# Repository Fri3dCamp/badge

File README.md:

# Fri3d Camp Badge 2018

De Badge voor Fri3d Camp 2018 is in volle ontwikkeling. Op dit ogenblik werken we aan het derde prototype, dat, als alles goed gaat nagenoeg de finale vorm zal hebben.

More to come ...

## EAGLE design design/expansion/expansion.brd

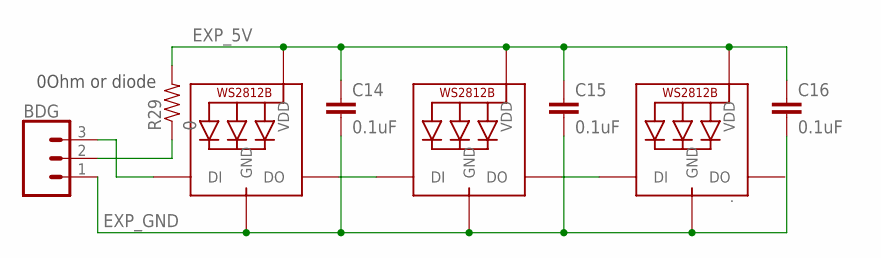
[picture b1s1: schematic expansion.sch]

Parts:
BDG: CONN_03; 1X03
C14, C15, C16: 0.1uF; 0805
R29: 0; 0805
WS1, WS2, WS3: WS2812B5050; WS2812B

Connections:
EXP_5V: C14.1, C15.1, C16.1, R29.2, WS1.1-VDD (VDD), WS2.1-VDD (VDD), WS3.1-VDD (VDD)
EXP_GND: BDG.1, C14.2, C15.2, C16.2, WS1.3-GND (GND), WS2.3-GND (GND), WS3.3-GND (GND)
unnamed: BDG.2, R29.1
unnamed: WS1.2-DOUT (DO), WS2.4-DIN (DI)
unnamed: WS2.2-DOUT (DO), WS3.4-DIN (DI)
unnamed: BDG.3, WS1.4-DIN (DI)

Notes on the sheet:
0Ohm or diode

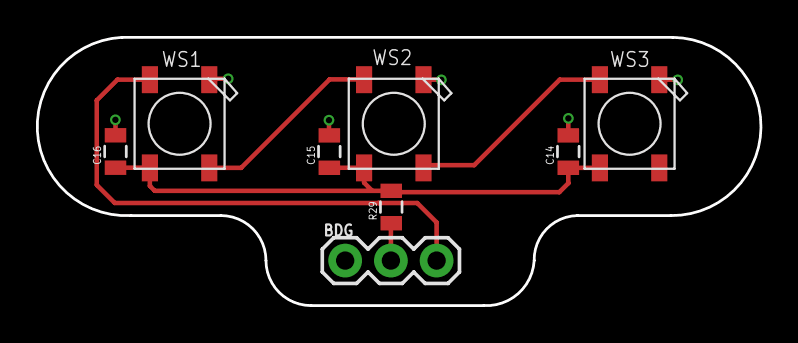
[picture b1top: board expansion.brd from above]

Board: 2 copper layers, 40.2 x 14.9 mm, 8 parts (0 on the bottom side), 6 nets.

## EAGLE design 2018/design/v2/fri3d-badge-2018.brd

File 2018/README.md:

# Fri3d Camp Badge 2018

De Badge voor Fri3d Camp 2018 is in volle ontwikkeling. Op dit ogenblik werken we aan het tweede prototype, dat, als alles goed gaat nagenoeg de finale vorm zal hebben.

More to come ...

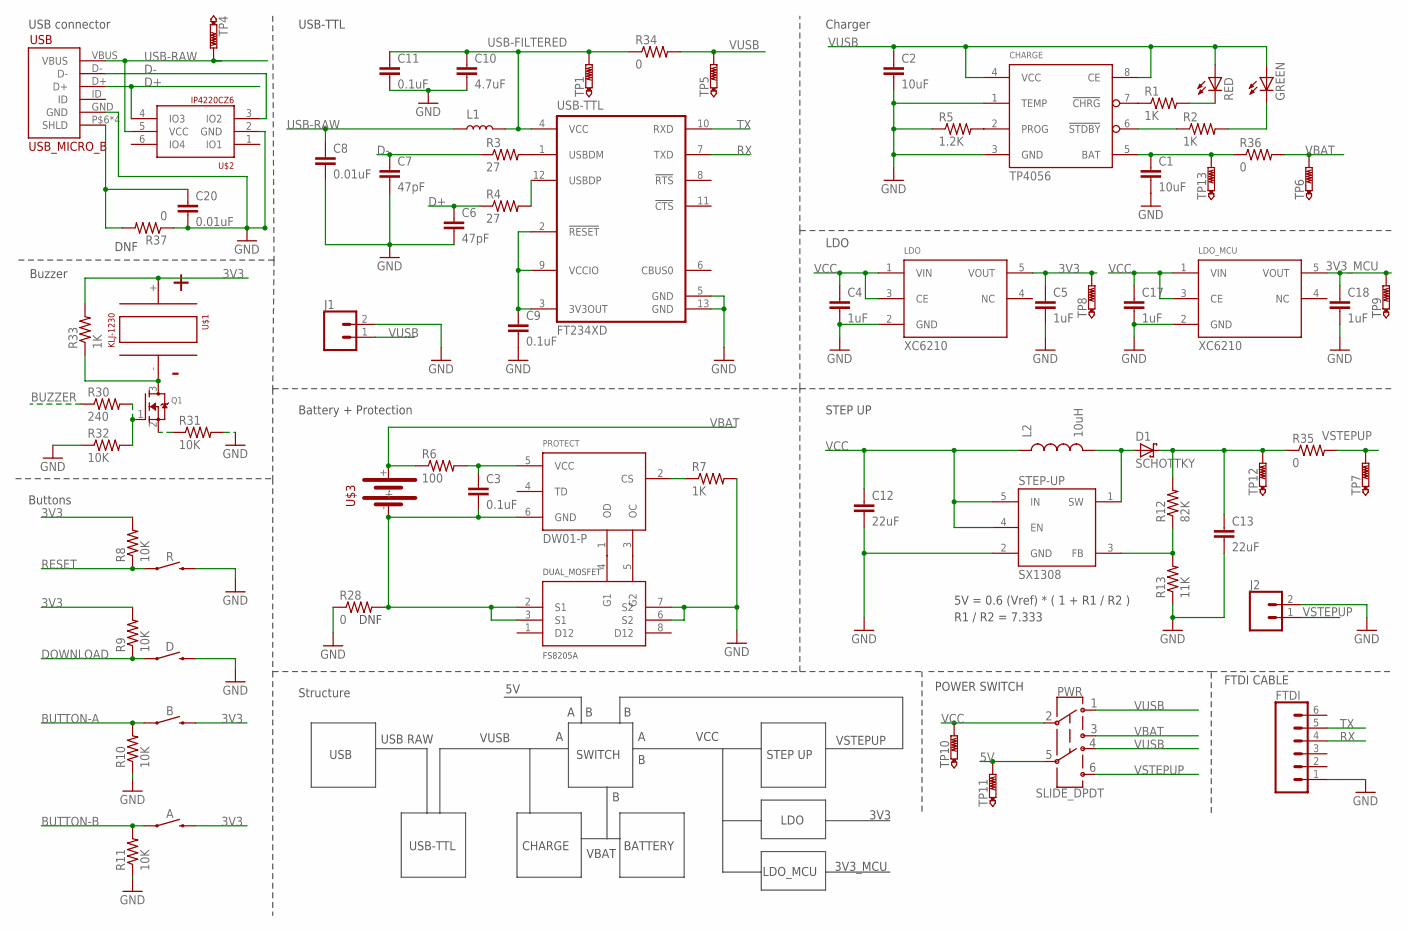
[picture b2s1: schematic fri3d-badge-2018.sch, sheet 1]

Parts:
A: SWITCH-MOMENTARY-4.5MM
B: SWITCH-MOMENTARY-4.5MM
C1, C2: 10uF; 0805
C3, C9, C11: 0.1uF; 0805
C4, C5, C17, C18: 1uF; 0805
C6, C7: 47pF; 0805
C8, C20: 0.01uF; 0805
C10: 4.7uF; 0805
C12, C13: 22uF; 0805
CHARGE: TP4056; SO8
D: SWITCH-MOMENTARY-4.5MM
D1: SCHOTTKY; SOD993
DUAL_MOSFET: FS8205A; TSSOP8
FTDI: CONN_06SILK_FEMALE_PTH; 1X06
GREEN: LEDCHIP-LED0805; CHIP-LED0805
J1, J2: CONN_02; 1X02
L1: INDUCTOR-0805-3.3UH; 0805
L2: 10uH; TYS6045
LDO: XC6210; SOT23-5
LDO_MCU: XC6210; SOT23-5
PROTECT: DW01-P; SOT23-6
PWR: SLIDE_DPDT; SLIDE_SWITCH
Q1: MOSFET-NREFLOW; SOT23
R: SWITCH-MOMENTARY-4.5MM
R1, R2, R7, R33: 1K; 0805
R3, R4: 27; 0805
R5: 1.2K; 0805
R6: 100; 0805
R8, R9, R10, R11, R31, R32: 10K; 0805
R12: 82K; 0805
R13: 11K; 0805
R28, R34, R35, R36, R37: 0; 0805
R30: 240; 0805
RED: LEDCHIP-LED0805; CHIP-LED0805
STEP-UP: SX1308; SOT23-6
TP1, TP4, TP5, TP6, TP7, TP8, TP9, TP10, TP11, TP12, TP13: PTR1B1,27; B1,27
U$1: KLJ-1230
U$2: IP4220CZ6; SOT457R_PHILIPS
U$3: CR18650; BATTERY_HOLDER_18650
USB: USB_MICRO_B
USB-TTL: FT234XD; DFN12

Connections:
3V3: A.3 (2), A.4 (2), B.3 (2), B.4 (2), C5.1, LDO.5 (VOUT), R8.2, R9.2, R33.2, TP8.TP, U$1.+; also elsewhere on the board
3V3_MCU: C18.1, LDO_MCU.5 (VOUT), TP9.TP; also elsewhere on the board
5V: PWR.5, TP11.TP; also elsewhere on the board
BUZZER: R30.1; also elsewhere on the board
D+: C6.1, R4.1, U$2.4 (IO3), USB.D+
D-: C7.1, R3.1, U$2.3 (IO2), USB.D-
DOWNLOAD: D.1, D.2 (1), R9.1; also elsewhere on the board
GND: C1.2, C2.2, C4.2, C5.2, C6.2, C7.2, C8.2, C9.2, C10.2, C11.2, C12.2, C13.2, C17.2, C18.2, C20.2, CHARGE.1 (TEMP), CHARGE.3 (GND), D.3 (2), D.4 (2), DUAL_MOSFET.6 (S2), DUAL_MOSFET.7 (S2), FTDI.1, J1.2, J2.2, LDO.2 (GND), LDO_MCU.2 (GND), R.3 (2), R.4 (2), R5.1, R7.2, R10.1, R11.1, R13.1, R28.1, R31.2, R32.1, R37.1, STEP-UP.2 (GND), U$2.2 (GND), USB.GND, USB-TTL.5 (GND), USB-TTL.13 (GND); also elsewhere on the board
unnamed: C13.1, D1.P$2 (C), R12.2, R35.1, TP12.TP
unnamed: Q1.3 (D), R33.1, U$1.-
unnamed: R3.2, USB-TTL.1 (USBDM)
unnamed: CHARGE.7 (!CHRG!), R1.1
unnamed: R4.2, USB-TTL.12 (USBDP)
unnamed: C9.1, USB-TTL.2 (!RESET!), USB-TTL.3 (3V3OUT), USB-TTL.9 (VCCIO)
unnamed: CHARGE.6 (!STDBY!), R2.1
unnamed: R1.2, RED.C
unnamed: GREEN.C, R2.2
unnamed: CHARGE.2 (PROG), R5.2
unnamed: Q1.1 (G), R30.2, R32.2
unnamed: PROTECT.2 (CS), R7.1
unnamed: C3.1, PROTECT.5 (VCC), R6.2
unnamed: DUAL_MOSFET.4 (G1), PROTECT.1 (OD)
unnamed: DUAL_MOSFET.5 (G2), PROTECT.3 (OC)
unnamed: R12.1, R13.2, STEP-UP.3 (FB)
unnamed: D1.P$1 (A), L2.P$2 (2), STEP-UP.1 (SW)
unnamed: C1.1, CHARGE.5 (BAT), R36.1, TP13.TP
unnamed: C20.1, R37.2, USB.P$6 (SHLD), USB.P$7 (SHLD), USB.P$8 (SHLD), USB.P$9 (SHLD)
unnamed: C3.2, DUAL_MOSFET.2 (S1), DUAL_MOSFET.3 (S1), PROTECT.6 (GND), R28.2, U$3.-
unnamed: Q1.2 (S), R31.1
RESET: R.1, R.2 (1), R8.1; also elsewhere on the board
RX: FTDI.4, USB-TTL.7 (TXD); also elsewhere on the board
TX: FTDI.5, USB-TTL.10 (RXD); also elsewhere on the board
USB-FILTERED: C10.1, C11.1, L1.2, R34.1, TP1.TP, USB-TTL.4 (VCC)
USB-RAW: C8.1, L1.1, TP4.TP, U$2.5 (VCC), USB.VBUS
VBAT: PWR.3, R6.1, R36.2, TP6.TP, U$3.+
VCC: C4.1, C12.1, C17.1, L2.P$1 (1), LDO.1 (VIN), LDO.3 (CE), LDO_MCU.1 (VIN), LDO_MCU.3 (CE), PWR.2, STEP-UP.4 (EN), STEP-UP.5 (IN), TP10.TP
VSTEPUP: J2.1, PWR.4 (6), R35.2, TP7.TP
VUSB: C2.1, CHARGE.4 (VCC), CHARGE.8 (CE), GREEN.A, J1.1, PWR.1, PWR.8 (4), R34.2, RED.A, TP5.TP

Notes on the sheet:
USB connector
Charger
USB-TTL
Battery + Protection
LDO
POWER SWITCH
Buttons
STEP UP
USB
USB RAW
VUSB
CHARGE
VBAT
BATTERY
Structure
VCC
SWITCH
3V3
VSTEPUP
5V = 0.6 (Vref) * ( 1 + R1 / R2 )
R1 / R2 = 7.333
DNF
FTDI CABLE
LDO_MCU
3V3_MCU
Buzzer

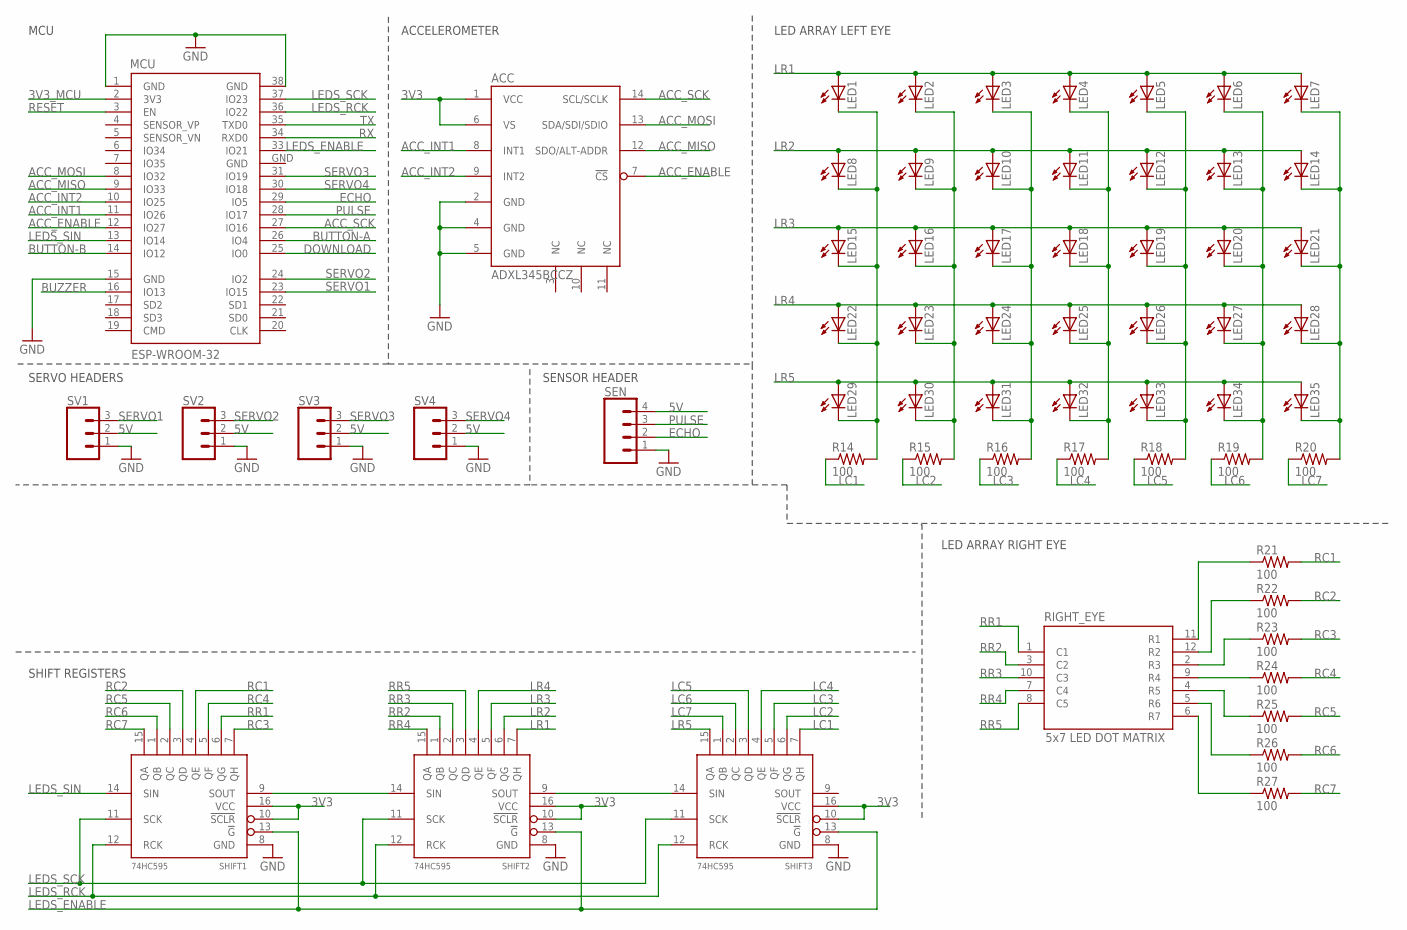
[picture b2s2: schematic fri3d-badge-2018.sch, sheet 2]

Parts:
ACC: ADXL345BCCZ; LGA
LED1, LED2, LED3, LED4, LED5, LED6, LED7, LED8, LED9, LED10, LED11, LED12, LED13, LED14, LED15, LED16, LED17, LED18, LED19, LED20, LED21, LED22, LED23, LED24, LED25, LED26, LED27, LED28, LED29, LED30, LED31, LED32, LED33, LED34, LED35: LEDCHIP-LED0805; CHIP-LED0805
MCU: ESP-WROOM-32
R14, R15, R16, R17, R18, R19, R20, R21, R22, R23, R24, R25, R26, R27: 100; 0805
RIGHT_EYE: 5x7 LED DOT MATRIX; 5X7_DOT_LED_MATRIX
SEN: CONN_04; 1X04
SHIFT1, SHIFT2, SHIFT3: 74HC595; SO16
SV1, SV2, SV3, SV4: CONN_03; 1X03

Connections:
3V3: ACC.1 (VCC), ACC.6 (VS), SHIFT1.10 (!SCLR), SHIFT1.16 (VCC), SHIFT2.10 (!SCLR), SHIFT2.16 (VCC), SHIFT3.10 (!SCLR), SHIFT3.16 (VCC); also elsewhere on the board
3V3_MCU: MCU.2 (3V3); also elsewhere on the board
5V: SEN.4, SV1.2, SV2.2, SV3.2, SV4.2; also elsewhere on the board
ACC_ENABLE: ACC.7 (!CS!), MCU.12 (IO27)
ACC_INT1: ACC.8 (INT1), MCU.11 (IO26)
ACC_INT2: ACC.9 (INT2), MCU.10 (IO25)
ACC_MISO: ACC.12 (SDO/ALT-ADDR), MCU.9 (IO33)
ACC_MOSI: ACC.13 (SDA/SDI/SDIO), MCU.8 (IO32)
ACC_SCK: ACC.14 (SCL/SCLK), MCU.27 (IO16)
BUZZER: MCU.16 (IO13); also elsewhere on the board
DOWNLOAD: MCU.25 (IO0); also elsewhere on the board
ECHO: MCU.29 (IO5), SEN.2
GND: ACC.2 (GND), ACC.4 (GND), ACC.5 (GND), MCU.1 (GND), MCU.15 (GND), MCU.38 (GND), MCU.GND, SEN.1, SHIFT1.8 (GND), SHIFT2.8 (GND), SHIFT3.8 (GND), SV1.1, SV2.1, SV3.1, SV4.1; also elsewhere on the board
LC1: R14.1, SHIFT3.7 (QH)
LC2: R15.1, SHIFT3.6 (QG)
LC3: R16.1, SHIFT3.5 (QF)
LC4: R17.1, SHIFT3.4 (QE)
LC5: R18.1, SHIFT3.3 (QD)
LC6: R19.1, SHIFT3.2 (QC)
LC7: R20.1, SHIFT3.1 (QB)
LEDS_ENABLE: MCU.33 (IO21), SHIFT1.13 (!G), SHIFT2.13 (!G), SHIFT3.13 (!G)
LEDS_RCK: MCU.36 (IO22), SHIFT1.12 (RCK), SHIFT2.12 (RCK), SHIFT3.12 (RCK)
LEDS_SCK: MCU.37 (IO23), SHIFT1.11 (SCK), SHIFT2.11 (SCK), SHIFT3.11 (SCK)
LEDS_SIN: MCU.13 (IO14), SHIFT1.14 (SIN)
LR1: LED1.A, LED2.A, LED3.A, LED4.A, LED5.A, LED6.A, LED7.A, SHIFT2.7 (QH)
LR2: LED8.A, LED9.A, LED10.A, LED11.A, LED12.A, LED13.A, LED14.A, SHIFT2.6 (QG)
LR3: LED15.A, LED16.A, LED17.A, LED18.A, LED19.A, LED20.A, LED21.A, SHIFT2.5 (QF)
LR4: LED22.A, LED23.A, LED24.A, LED25.A, LED26.A, LED27.A, LED28.A, SHIFT2.4 (QE)
LR5: LED29.A, LED30.A, LED31.A, LED32.A, LED33.A, LED34.A, LED35.A, SHIFT3.15 (QA)
unnamed: SHIFT1.9 (SOUT), SHIFT2.14 (SIN)
unnamed: SHIFT2.9 (SOUT), SHIFT3.14 (SIN)
unnamed: R21.1, RIGHT_EYE.11 (R1)
unnamed: R22.1, RIGHT_EYE.12 (R2)
unnamed: LED1.C, LED8.C, LED15.C, LED22.C, LED29.C, R14.2
unnamed: LED2.C, LED9.C, LED16.C, LED23.C, LED30.C, R15.2
unnamed: LED3.C, LED10.C, LED17.C, LED24.C, LED31.C, R16.2
unnamed: LED4.C, LED11.C, LED18.C, LED25.C, LED32.C, R17.2
unnamed: LED5.C, LED12.C, LED19.C, LED26.C, LED33.C, R18.2
unnamed: LED6.C, LED13.C, LED20.C, LED27.C, LED34.C, R19.2
unnamed: LED7.C, LED14.C, LED21.C, LED28.C, LED35.C, R20.2
unnamed: R24.1, RIGHT_EYE.9 (R4)
unnamed: R23.1, RIGHT_EYE.2 (R3)
unnamed: R25.1, RIGHT_EYE.4 (R5)
unnamed: R26.1, RIGHT_EYE.5 (R6)
unnamed: R27.1, RIGHT_EYE.6 (R7)
PULSE: MCU.28 (IO17), SEN.3
RC1: R21.2, SHIFT1.4 (QE)
RC2: R22.2, SHIFT1.3 (QD)
RC3: R23.2, SHIFT1.7 (QH)
RC4: R24.2, SHIFT1.5 (QF)
RC5: R25.2, SHIFT1.2 (QC)
RC6: R26.2, SHIFT1.1 (QB)
RC7: R27.2, SHIFT1.15 (QA)
RESET: MCU.3 (EN); also elsewhere on the board
RR1: RIGHT_EYE.1 (C1), SHIFT1.6 (QG)
RR2: RIGHT_EYE.3 (C2), SHIFT2.1 (QB)
RR3: RIGHT_EYE.10 (C3), SHIFT2.2 (QC)
RR4: RIGHT_EYE.7 (C4), SHIFT2.15 (QA)
RR5: RIGHT_EYE.8 (C5), SHIFT2.3 (QD)
RX: MCU.34 (RXD0); also elsewhere on the board
SERVO1: MCU.23 (IO15), SV1.3
SERVO2: MCU.24 (IO2), SV2.3
SERVO3: MCU.31 (IO19), SV3.3
SERVO4: MCU.30 (IO18), SV4.3
TX: MCU.35 (TXD0); also elsewhere on the board

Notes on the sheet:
LED ARRAY LEFT EYE
LED ARRAY RIGHT EYE
SHIFT REGISTERS
MCU
ACCELEROMETER
SERVO HEADERS
SENSOR HEADER

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
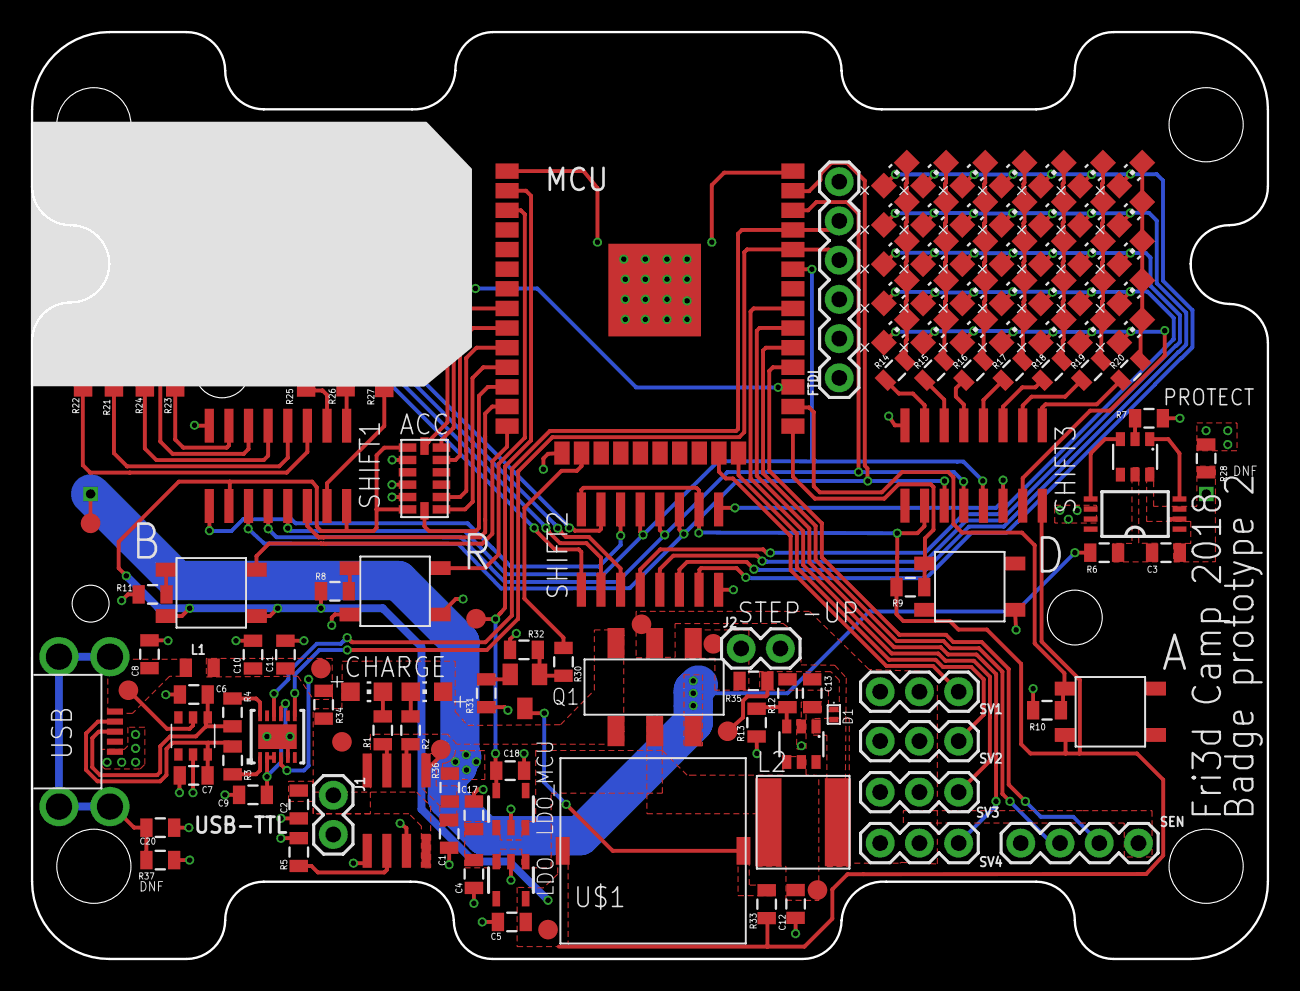
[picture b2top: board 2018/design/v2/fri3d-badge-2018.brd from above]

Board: 2 copper layers, 80.0 x 60.0 mm, 134 parts (1 on the bottom side), 96 nets.

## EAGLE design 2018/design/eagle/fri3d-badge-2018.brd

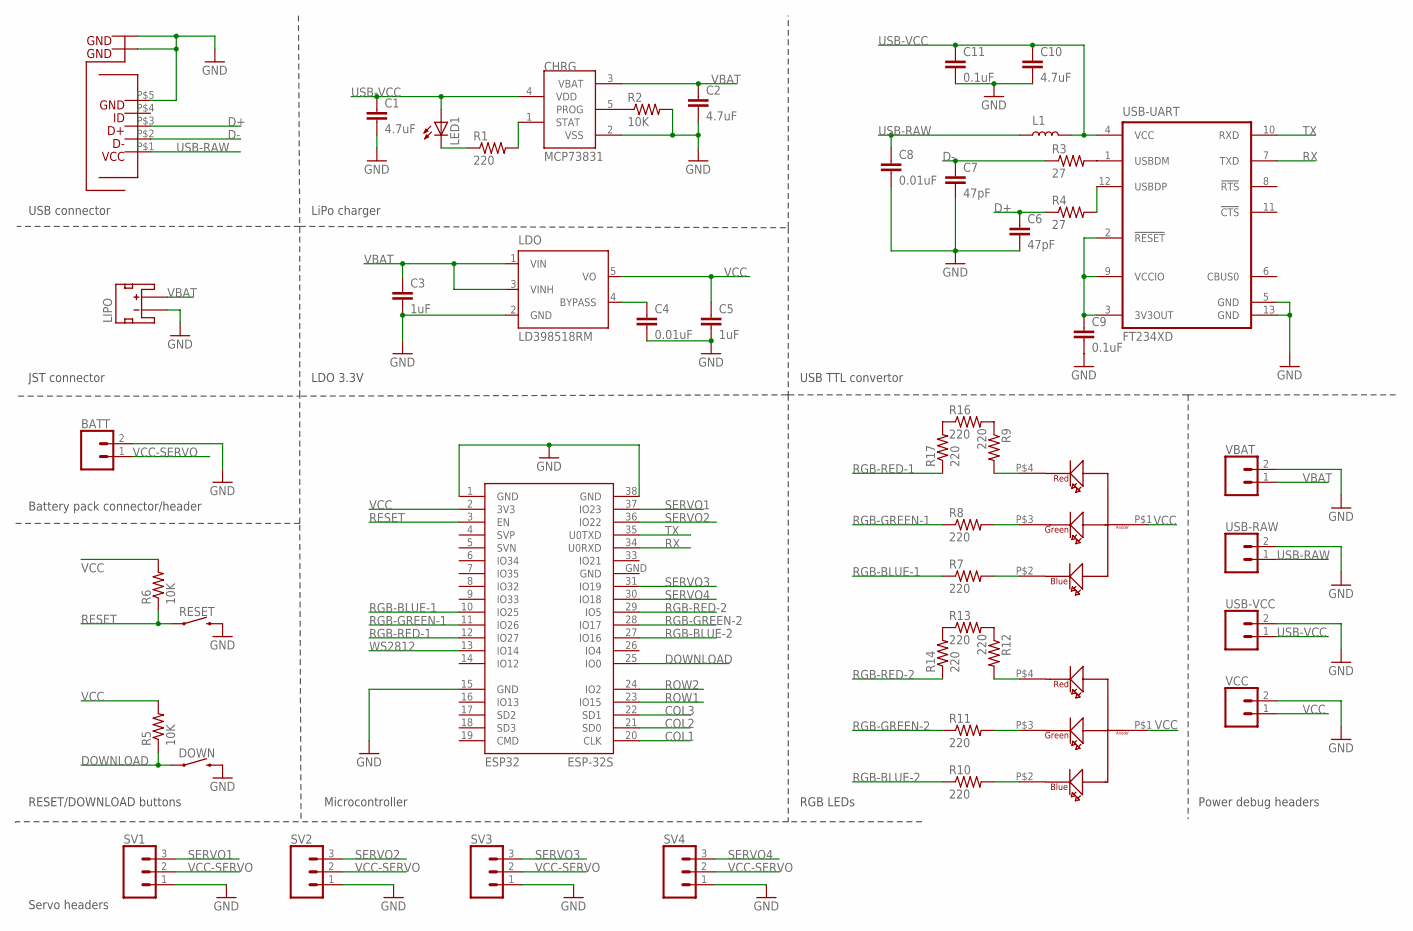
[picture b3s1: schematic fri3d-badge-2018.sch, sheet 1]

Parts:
BATT: CONN_02; 1X02
C1, C2, C10: 4.7uF; 0805
C3, C5: 1uF; 0805
C4, C8: 0.01uF; 0805
C6, C7: 47pF; 0805
C9, C11: 0.1uF; 0805
CHRG: MCP73831; SOT23-5L
DOWN: MOMENTARY-SWITCH-SPST-PTH-6.0MM; TACTILE_SWITCH_PTH_6.0MM
ESP32: ESP-32S
L1: INDUCTOR-0805-3.3UH; 0805
LDO: LD398518RM; SOT23-5L
LED1: LEDCHIP-LED0805; CHIP-LED0805
LIPO: JST_2MM_MALE; JST-2-SMD
R1, R7, R8, R9, R10, R11, R12, R13, R14, R16, R17: 220; 0805
R2, R5, R6: 10K; 0805
R3, R4: 27; 0805
RESET: MOMENTARY-SWITCH-SPST-PTH-6.0MM; TACTILE_SWITCH_PTH_6.0MM
SV1, SV2, SV3, SV4: CONN_03; 1X03
U$1, U$4: DRAGAN-PERSONAL_AVAGO-RGB-LED
U$5: OCTA-CORE_MCIRO-USB2MOUSER; OCTA-CORE_MICRO-USB2
USB-RAW: CONN_02; 1X02
USB-UART: FT234XD; DFN12
USB-VCC: CONN_02; 1X02
VBAT: CONN_02; 1X02
VCC: CONN_02; 1X02

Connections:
COL1: ESP32.20 (CLK); also elsewhere on the board
COL2: ESP32.21 (SD0); also elsewhere on the board
COL3: ESP32.22 (SD1); also elsewhere on the board
D+: C6.1, R4.1, U$5.P$3
D-: C7.1, R3.1, U$5.P$2
DOWNLOAD: DOWN.1, ESP32.25 (IO0), R5.1
GND: BATT.2, C1.2, C2.2, C3.2, C4.2, C5.2, C6.2, C7.2, C8.2, C9.2, C10.2, C11.2, CHRG.2 (VSS), DOWN.3 (2), ESP32.1 (GND), ESP32.15 (GND), ESP32.38 (GND), ESP32.GND, LDO.2 (GND), LIPO.1 (-), R2.2, RESET.3 (2), SV1.1, SV2.1, SV3.1, SV4.1, U$5.P$5, U$5.P$6, U$5.P$7, U$5.P$8, U$5.P$9, U$5.P$10, U$5.P$11, U$5.P$12, U$5.P$13, USB-RAW.2, USB-UART.5 (GND), USB-UART.13 (GND), USB-VCC.2, VBAT.2, VCC.2; also elsewhere on the board
unnamed: CHRG.5 (PROG), R2.1
unnamed: R3.2, USB-UART.1 (USBDM)
unnamed: CHRG.1 (STAT), R1.2
unnamed: LED1.C, R1.1
unnamed: R4.2, USB-UART.12 (USBDP)
unnamed: C9.1, USB-UART.2 (!RESET!), USB-UART.3 (3V3OUT), USB-UART.9 (VCCIO)
unnamed: C4.1, LDO.4 (BYPASS)
unnamed: R12.1, R13.2
unnamed: R13.1, R14.2
unnamed: R11.2, U$1.P$3
unnamed: R9.1, R16.2
unnamed: R16.1, R17.2
unnamed: R12.2, U$1.P$4
unnamed: R10.2, U$1.P$2
unnamed: R9.2, U$4.P$4
unnamed: R8.2, U$4.P$3
unnamed: R7.2, U$4.P$2
RESET: ESP32.3 (EN), R6.1, RESET.1
RGB-BLUE-1: ESP32.10 (IO25), R7.1
RGB-BLUE-2: ESP32.27 (IO16), R10.1
RGB-GREEN-1: ESP32.11 (IO26), R8.1
RGB-GREEN-2: ESP32.28 (IO17), R11.1
RGB-RED-1: ESP32.12 (IO27), R17.1
RGB-RED-2: ESP32.29 (IO5), R14.1
ROW1: ESP32.23 (IO15); also elsewhere on the board
ROW2: ESP32.24 (IO2); also elsewhere on the board
RX: ESP32.34 (U0RXD), USB-UART.7 (TXD)
SERVO1: ESP32.37 (IO23), SV1.3
SERVO2: ESP32.36 (IO22), SV2.3
SERVO3: ESP32.31 (IO19), SV3.3
SERVO4: ESP32.30 (IO18), SV4.3
TX: ESP32.35 (U0TXD), USB-UART.10 (RXD)
USB-RAW: C8.1, L1.1, U$5.P$1, USB-RAW.1
USB-VCC: C1.1, C10.1, C11.1, CHRG.4 (VDD), L1.2, LED1.A, USB-UART.4 (VCC), USB-VCC.1
VBAT: C2.1, C3.1, CHRG.3 (VBAT), LDO.1 (VIN), LDO.3 (VINH), LIPO.2 (+), VBAT.1
VCC: C5.1, ESP32.2 (3V3), LDO.5 (VO), R5.2, R6.2, U$1.P$1, U$4.P$1, VCC.1; also elsewhere on the board
VCC-SERVO: BATT.1, SV1.2, SV2.2, SV3.2, SV4.2
WS2812: ESP32.13 (IO14); also elsewhere on the board

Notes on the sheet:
USB connector
LiPo charger
USB TTL convertor
LDO 3.3V
JST connector
RESET/DOWNLOAD buttons
Microcontroller
RGB LEDs
Servo headers
Power debug headers
Battery pack connector/header

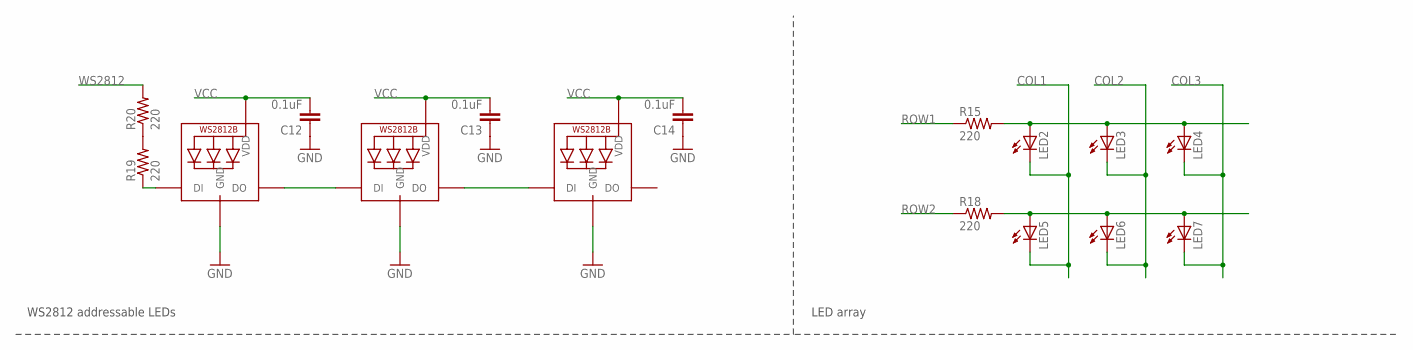
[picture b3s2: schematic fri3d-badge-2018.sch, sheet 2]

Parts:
C12, C13, C14: 0.1uF; 0805
LED2, LED3, LED4, LED5, LED6, LED7: LEDCHIP-LED0805; CHIP-LED0805
R15, R18, R19, R20: 220; 0805
WS1, WS2, WS3: WS2812B5050; WS2812B

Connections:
COL1: LED2.C, LED5.C; also elsewhere on the board
COL2: LED3.C, LED6.C; also elsewhere on the board
COL3: LED4.C, LED7.C; also elsewhere on the board
GND: C12.1, C13.1, C14.1, WS1.3-GND (GND), WS2.3-GND (GND), WS3.3-GND (GND); also elsewhere on the board
unnamed: WS1.2-DOUT (DO), WS2.4-DIN (DI)
unnamed: WS2.2-DOUT (DO), WS3.4-DIN (DI)
unnamed: LED2.A, LED3.A, LED4.A, R15.2
unnamed: LED5.A, LED6.A, LED7.A, R18.2
unnamed: R19.1, WS1.4-DIN (DI)
unnamed: R19.2, R20.1
ROW1: R15.1; also elsewhere on the board
ROW2: R18.1; also elsewhere on the board
VCC: C12.2, C13.2, C14.2, WS1.1-VDD (VDD), WS2.1-VDD (VDD), WS3.1-VDD (VDD); also elsewhere on the board
WS2812: R20.2; also elsewhere on the board

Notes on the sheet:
WS2812 addressable LEDs
LED array

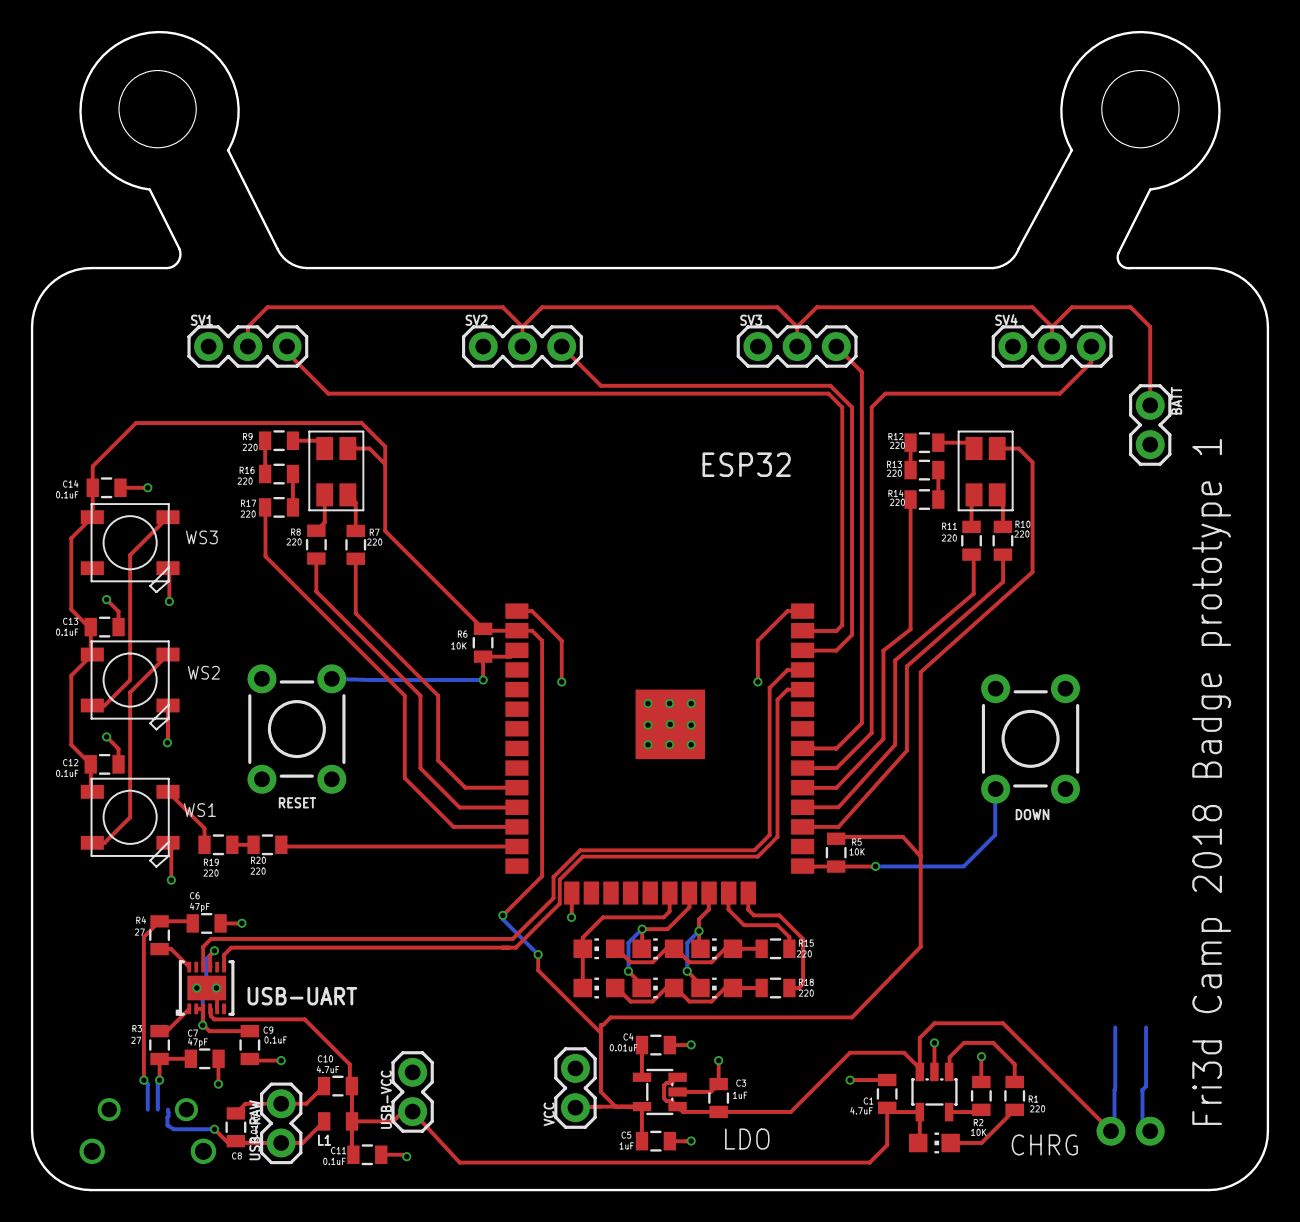
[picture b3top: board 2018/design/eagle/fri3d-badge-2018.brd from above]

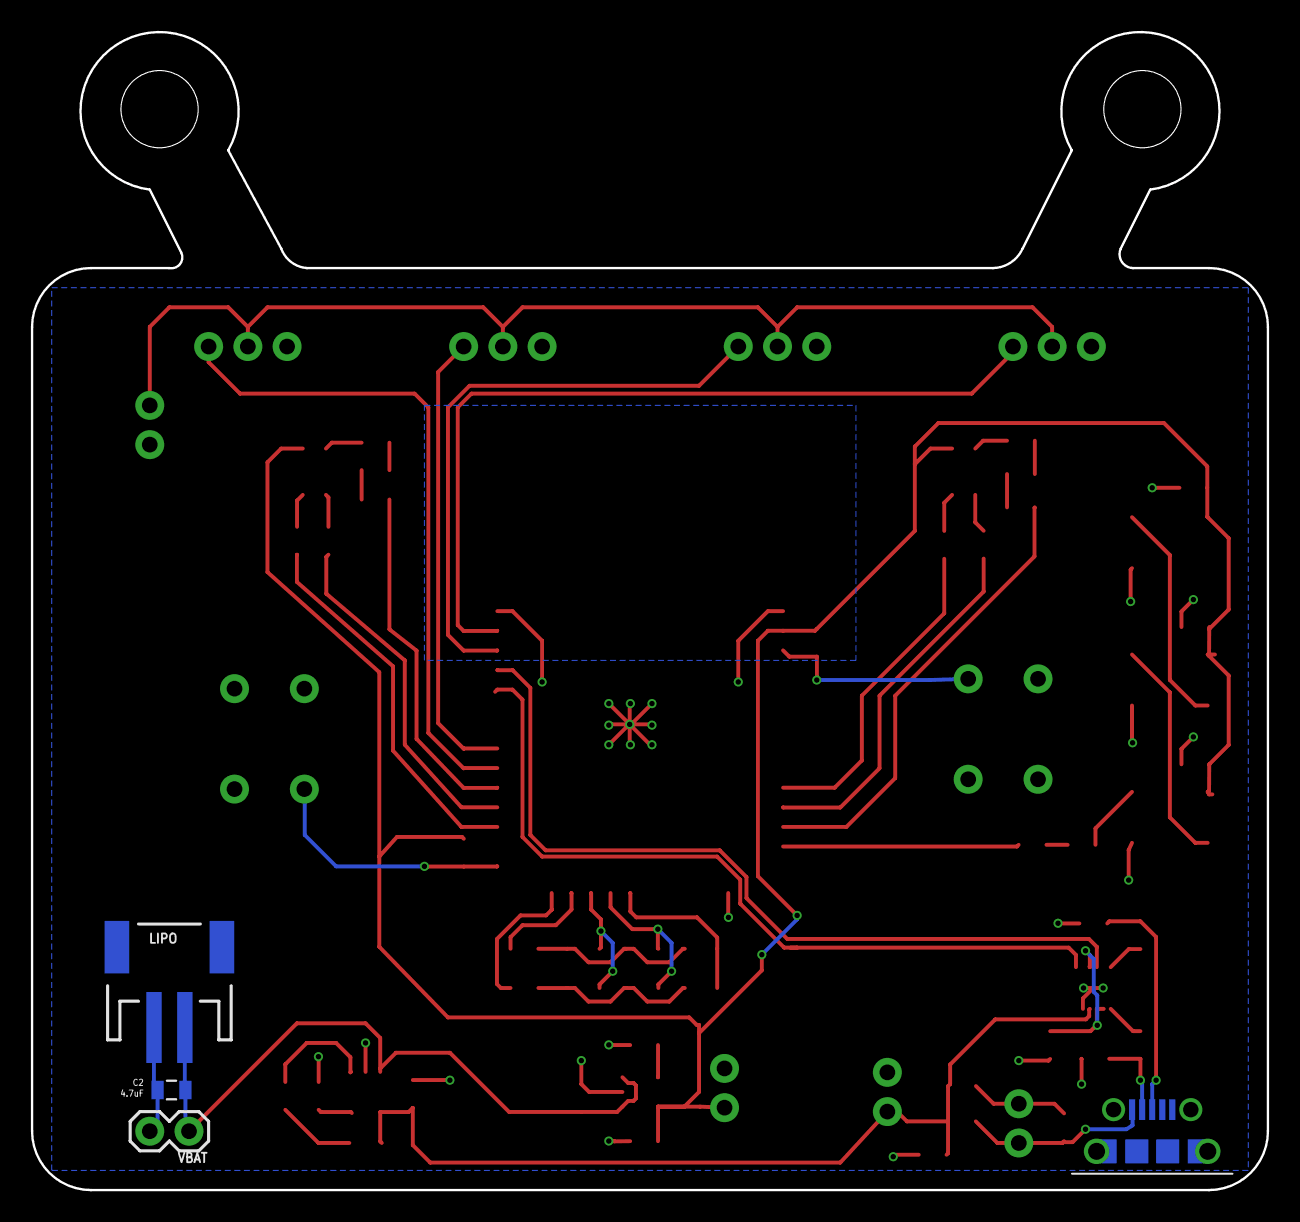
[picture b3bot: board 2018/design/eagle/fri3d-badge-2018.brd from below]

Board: 2 copper layers, 80.0 x 75.0 mm, 64 parts (4 on the bottom side), 51 nets.

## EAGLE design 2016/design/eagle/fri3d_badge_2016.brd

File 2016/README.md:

# Fri3d Camp Badge 2016

Bij het ontwerp van de badge voor Fri3d Camp 2016 zijn we vertrokken van drie principes:

1. Een hoge _hack_-baarheid.
2. Leerzaam voor beginners.
3. Interactief.

Daarom brengt de badge het Arduino platform samen met infra-rode stralen om een eenvoudig Fri3d Camp draadloos (IR) netwerk te maken.

Het Arduino platform laat iedereen toe om de software van de badge aan te passen, of er iets totaal anders mee te doen. Naast de badge-functie voor Fri3d Camp, brengen we alle andere mogelijke functionaliteit van de microcontroller naar buiten, zodat de badge, na het kamp, letterlijk kan dienen als jouw eigen Arduino ontwikkel-bord.

Aan de hand van de IR componenten en bijhorende software kunnen de elementaire aspecten van draadloze communicatie uitgelegd worden.

### Meta-Leerzaam

Dit ontwerp was mijn eerste SMD-gebaseerde project en het is op zich al een leerzame ervaring. Daarom bevat deze repository tevens een [design dagboek](design/dagboek.md) waarin ik alle stappen van het proces beschrijf.

## Hardware Design

Twee bestaande projecten kunnen beschouwd worden als de spreekwoordelijke ouders van de badge: 

* [Arduino Pro Micro - 3.3V/8MHz van Sparkfun](https://www.sparkfun.com/products/12587)
* [TV B Gone van Mitch Altman](https://cornfieldelectronics.com/tvbgone/tvbg.home.php)

Voeg nog een IR receiver en een RGB LED toe en je hebt alle basis componenten voor een leerzame, interactieve en zeer _hack_-bare Fri3d Camp badge!

## Software

Om zelf aan de slag te gaan met de [software](src/README.md) zo eenvoudig mogelijk te maken, was één van dé belangrijkste aspecten een makkelijke integratie met het Arduino software platform. De mogelijkheid om de badge te programmeren via de Arduino IDE door middel van louter een micro-USB kabel was daarom een noodzaak.

Om het Arduino platform nog verder zo veel mogelijk te gebruiken, hebben we ook gekozen om zo dicht mogelijk bij een bestaand Arduino bord te blijven en zo is de badge in essentie een [Arduino Mirco](https://www.arduino.cc/en/Main/ArduinoBoardMicro) geworden.

Je kan dus onmiddellijk aan de slag, zoals met elke andere Arduino. Daarnaast bevat deze [repository](src/README.md) enkele applicaties specifiek geschreven voor de Fri3d Camp badge, en dit naast een bibliotheek die het aanspreken van de extras makkelijk maakt. Zo vindt je hier:

* dé Fri3d Camp 2016 app
* een implementatie van de TV B Gone applicatie van Mitch Altman
* ...

Als je zelf een nieuwe app maakt die op de Fri3d Camp badge werkt en op een andere, leuke manier gebruik maakt van de IR communicatie en de RGB LED of van andere componenten die je er zelf aan toegevoegd hebt, bezorg ons dan deze code en we voegen ze toe aan deze repository (pull request).

## Credits

De badge werd ontworpen door Christophe VG, samen met de hele Fri3d Camp organisatie, en uitgewerkt met de hulp van Dragan Subotic, Yannick Verbelen, Maarten Weyn, Willy De a Court, Anthony Liekens, Dries Deroeck, Jef Van Den Broeck, Toon Van de Putte,...

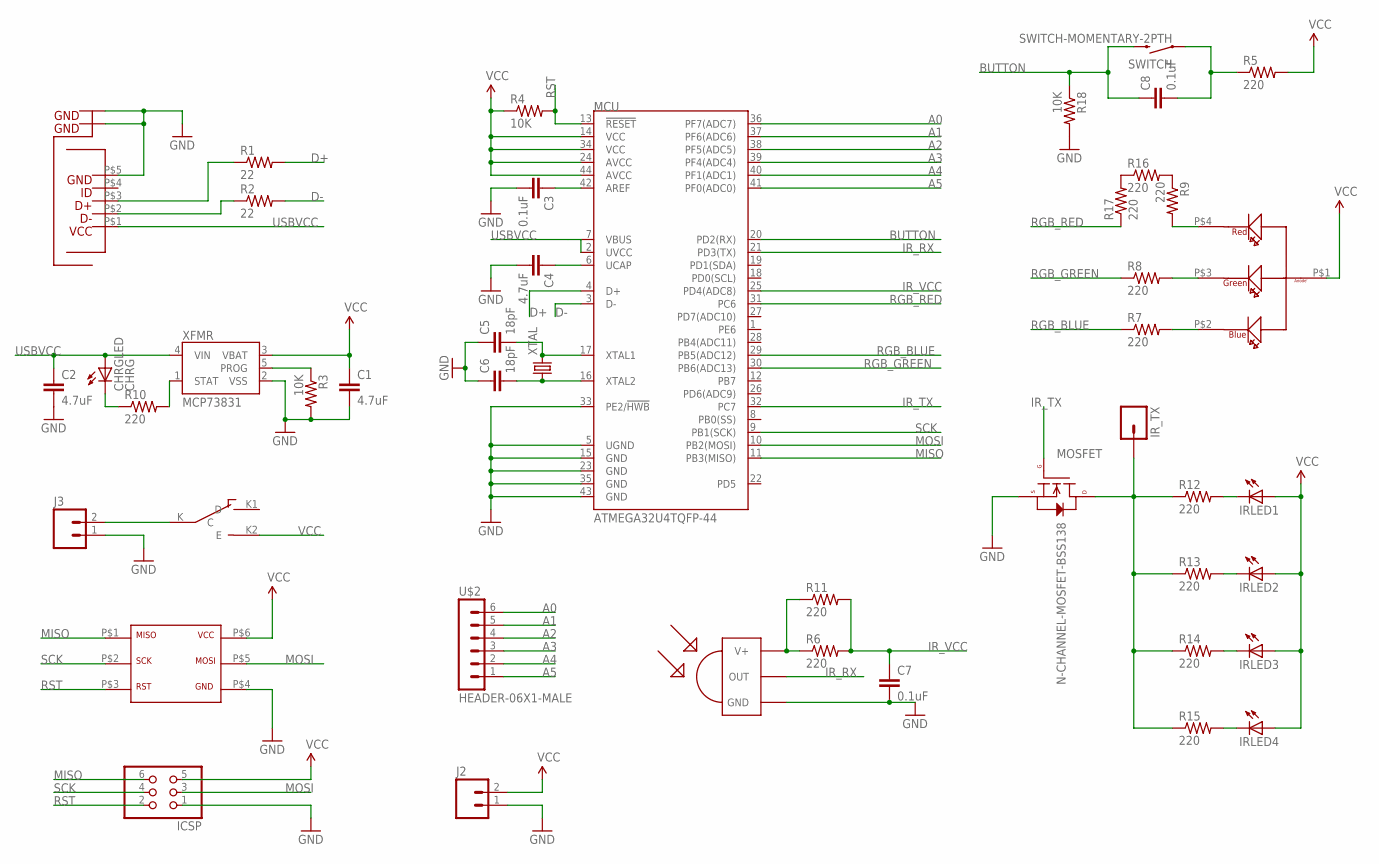
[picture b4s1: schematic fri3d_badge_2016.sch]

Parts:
C1, C2, C4: 4.7uF; 0805
C3, C7, C8: 0.1uF; 0805
C5, C6: 18pF; 0805
CHRGLED: CHRG; CHIPLED_0805
ICSP: PINHD-2X3; 2X03
IRLED1, IRLED2, IRLED3, IRLED4: LEDCHIPLED_0805; CHIPLED_0805
IR_TX: M01PTH; 1X01
J2: M02PTH; 1X02
J3: M02JST-PTH-2; JST-2-PTH
MCU: ATMEGA32U4TQFP-44; TQFP44
MOSFET: N-CHANNEL-MOSFET-BSS138; SOT23-3
R1, R2: 22; 0805
R3, R4, R18: 10K; 0805
R5, R6, R7, R8, R9, R10, R11, R12, R13, R14, R15, R16, R17: 220; 0805
SWITCH: SWITCH-MOMENTARY-2PTH; TACTILE-PTH
U$2: HEADER-06X1-MALE; 06X1-PTH
U$3: TSOP4838; TSOP18XX
U$4: DRAGAN-PERSONAL_AVAGO-RGB-LED
U$5: OCTA-CORE_MCIRO-USB2MOUSER; OCTA-CORE_MICRO-USB2
U$6: SLIDE-SWITCH
U$7: OCTA-CORE_TC2030-IDC
XFMR: MCP73831; SOT23-5
XTAL: CRYSTALHC49S; HC49/S

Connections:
A0: MCU.36 (PF7(ADC7)), U$2.6
A1: MCU.37 (PF6(ADC6)), U$2.5
A2: MCU.38 (PF5(ADC5)), U$2.4
A3: MCU.39 (PF4(ADC4)), U$2.3
A4: MCU.40 (PF1(ADC1)), U$2.2
A5: MCU.41 (PF0(ADC0)), U$2.1
BUTTON: C8.1, MCU.20 (PD2(RX)), R18.1, SWITCH.3 (2)
D+: MCU.4 (D+), R1.2
D-: MCU.3 (D-), R2.2
GND: C1.2, C2.2, C3.2, C4.2, C5.1, C6.1, C7.2, ICSP.1, J2.1, J3.1, MCU.5 (UGND), MCU.15 (GND), MCU.23 (GND), MCU.33 (PE2/!HWB), MCU.35 (GND), MCU.43 (GND), MOSFET.2 (S), R3.2, R18.2, U$3.GND, U$5.P$5, U$5.P$6, U$5.P$7, U$5.P$8, U$5.P$9, U$5.P$10, U$5.P$11, U$5.P$12, U$5.P$13, U$7.P$4, XFMR.2 (VSS)
IR_RX: MCU.21 (PD3(TX)), U$3.OUT
IR_TX: MCU.32 (PC7), MOSFET.1 (G)
IR_VCC: C7.1, MCU.25 (PD4(ADC8)), R6.2, R11.2
MISO: ICSP.6, MCU.11 (PB3(MISO)), U$7.P$1
MOSI: ICSP.3, MCU.10 (PB2(MOSI)), U$7.P$5
unnamed: R2.1, U$5.P$2
unnamed: R1.1, U$5.P$3
unnamed: C8.2, R5.1, SWITCH.1
unnamed: C4.1, MCU.6 (UCAP)
unnamed: R3.1, XFMR.5 (PROG)
unnamed: CHRGLED.C, R10.1
unnamed: C3.1, MCU.42 (AREF)
unnamed: C5.2, MCU.17 (XTAL1), XTAL.2
unnamed: C6.2, MCU.16 (XTAL2), XTAL.1
unnamed: R6.1, R11.1, U$3.VCC (V+)
unnamed: R9.1, R16.2
unnamed: R16.1, R17.2
unnamed: IRLED1.C, R12.2
unnamed: IRLED2.C, R13.2
unnamed: IRLED3.C, R14.2
unnamed: IRLED4.C, R15.2
unnamed: J3.2, U$6.K (C)
unnamed: R9.2, U$4.P$4
unnamed: R8.2, U$4.P$3
unnamed: R7.2, U$4.P$2
unnamed: R10.2, XFMR.1 (STAT)
unnamed: IR_TX.1, MOSFET.3 (D), R12.1, R13.1, R14.1, R15.1
RGB_BLUE: MCU.29 (PB5(ADC12)), R7.1
RGB_GREEN: MCU.30 (PB6(ADC13)), R8.1
RGB_RED: MCU.31 (PC6), R17.1
RST: ICSP.2, MCU.13 (!RESET), R4.2, U$7.P$3
SCK: ICSP.4, MCU.9 (PB1(SCK)), U$7.P$2
USBVCC: C2.1, CHRGLED.A, MCU.2 (UVCC), MCU.7 (VBUS), U$5.P$1, XFMR.4 (VIN)
VCC: C1.1, ICSP.5, IRLED1.A, IRLED2.A, IRLED3.A, IRLED4.A, J2.2, MCU.14 (VCC), MCU.24 (AVCC), MCU.34 (VCC), MCU.44 (AVCC), R4.1, R5.2, U$4.P$1, U$6.K2 (E), U$7.P$6, XFMR.3 (VBAT)

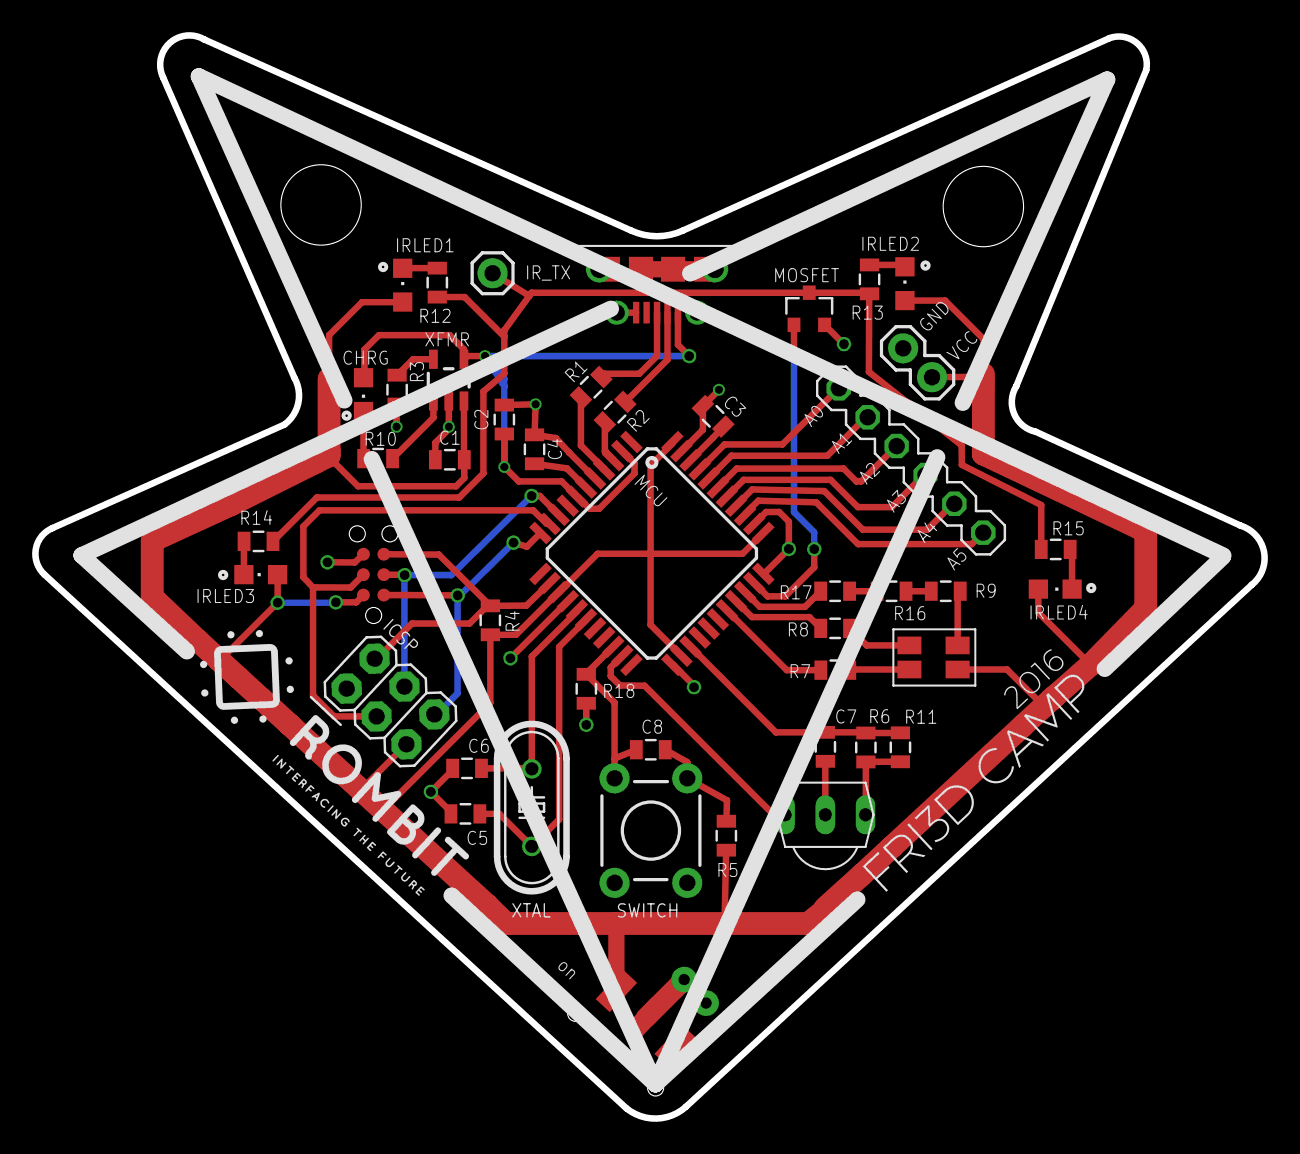
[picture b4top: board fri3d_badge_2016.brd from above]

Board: 2 copper layers, 76.5 x 67.4 mm, 46 parts (1 on the bottom side), 44 nets.

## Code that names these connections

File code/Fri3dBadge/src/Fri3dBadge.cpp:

#include "Fri3dBadge.h"

#include "config.h"

// IO controle pinnen voor de vier servo's, in volgorde van SERVO1,...
int pinnen[4] = { SERVO1_PIN, SERVO2_PIN, SERVO3_PIN, SERVO4_PIN };

Fri3dBadge::Fri3dBadge() 
{
	// creëer servo objecten voor de 4 servos
	// for(int i=0; i<4; i++) {
		// this->servos[i] = new Servo(pinnen[i]);
	// }
}

// Servo Fri3dBadge::servo(int index) {
	// return *(this->servos[index]);
// }

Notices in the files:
parts and their libraries:
SparkFun-Capacitors: Licensing: Creative Commons ShareAlike 4.0 International - https://creativecommons.org/licenses/by-sa/4.0
esp32: Creative Commons Attribution-ShareAlike 4.0 International
